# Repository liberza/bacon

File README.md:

# bacon - Balloon Ascent Controller

The goal of this project is to control the rate of ascent of two high-altitude
balloons, to keep at the same relative altitude as they ascend. 

A simulator is included in simulator/. Run tongs.py to start, then open client.html
in a browser. Power up the two payloads to begin auto-discovery. Once that is finished, 
the simulated flight begins and shows a live plot of progress.

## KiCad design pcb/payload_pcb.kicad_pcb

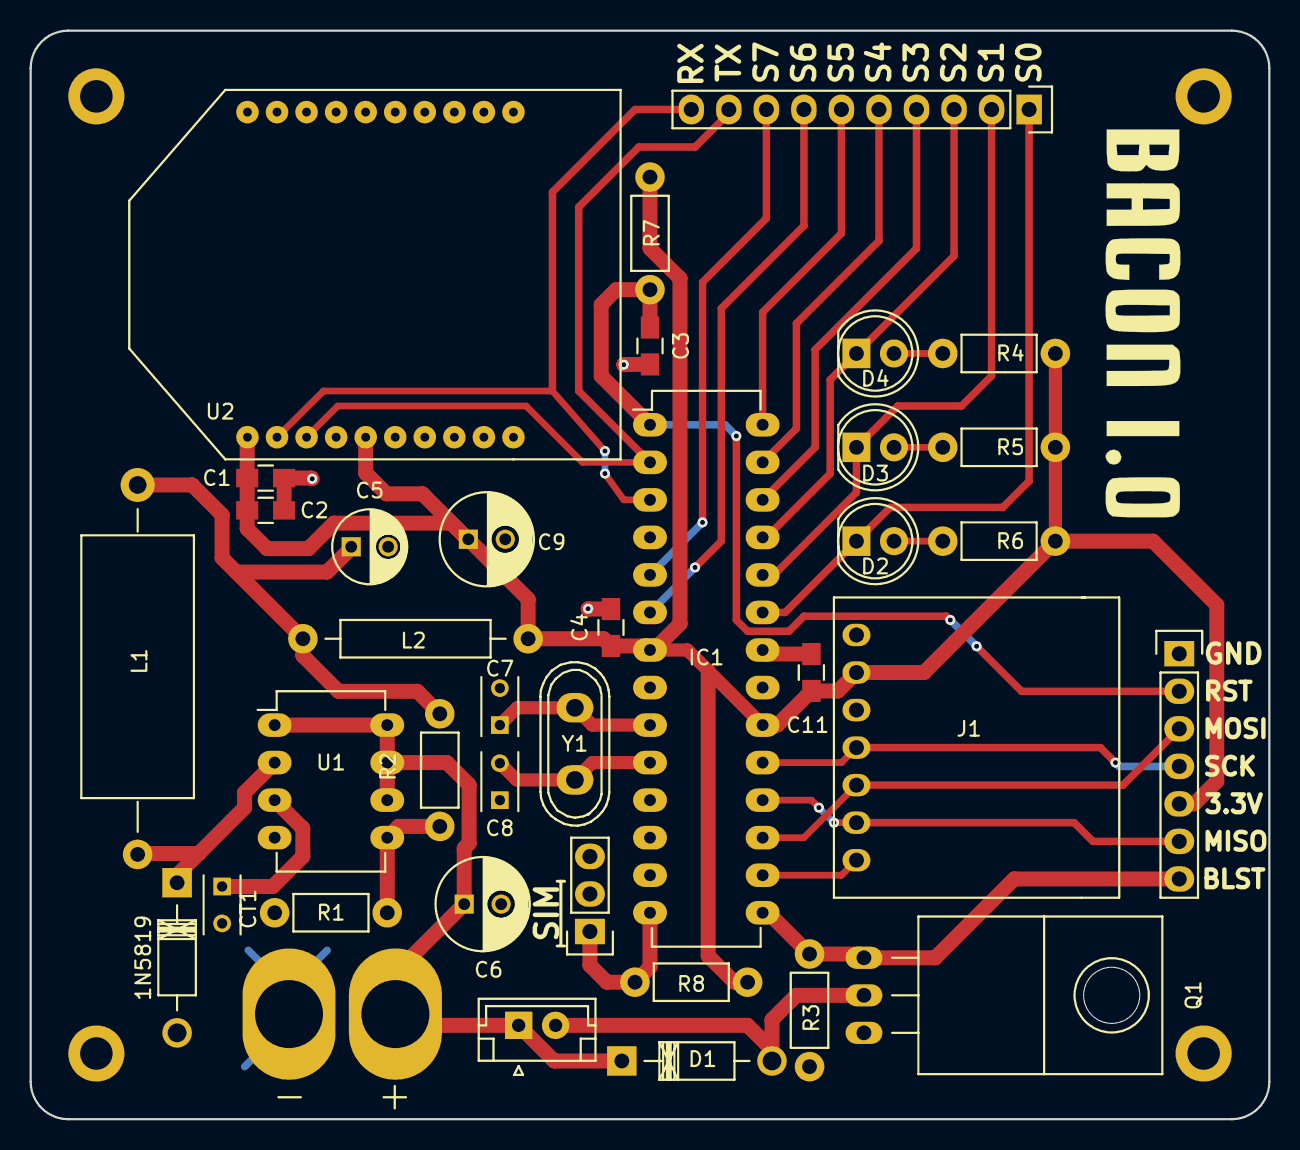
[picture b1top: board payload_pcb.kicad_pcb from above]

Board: 2 copper layers, 83.8 x 73.7 mm, 37 parts (0 on the bottom side), 30 nets.

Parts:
1N5819: D5; Diode_DO-41_SOD81_Horizontal_RM10
C1, C2, C4, C11: CP1; C_0805_HandSoldering
C3: 0.1uF; C_0805_HandSoldering
C5: 22uF; C_Radial_D5_L11_P2.5
C6: 100 uF; C_Radial_D6.3_L11.2_P2.5
C7, C8: 22p; C_Rect_L4_W2.5_P2.5
C9: 100uF; C_Radial_D6.3_L11.2_P2.5
CT1: 160 pF; C_Rect_L4_W2.5_P2.5
D1: D; Diode_DO-41_SOD81_Horizontal_RM10
D2: Green; LED-5MM
D3: Yellow; LED-5MM
D4: Red; LED-5MM
IC1: ATMEGA328-P; DIP-28_W7.62mm_LongPads
J1: MS5607_Module
L1: 50 uH; Choke_Horizontal_RM25mm
L2: 1 uH; Choke_Horizontal_RM15mm
P1: BAT_TERMINALS; XT60
P2: CONN_01X10; Pin_Header_Straight_1x10
P3: CONN_01X03; Pin_Header_Straight_1x03
P4: CONN_01X07; Pin_Header_Straight_1x07
P5: VALVE; JST_EH_B02B-EH-A_02x2.50mm_Straight
Q1: Q1; TO-220_Neutral123_Horizontal
R1: 22k; Resistor_Horizontal_RM7mm
R2: 36k; Resistor_Horizontal_RM7mm
R3, R7: 4.7k; Resistor_Horizontal_RM7mm
R4, R5, R6: 270; Resistor_Horizontal_RM7mm
R8: 4.7K; Resistor_Horizontal_RM7mm
U1: MC33063A; DIP-8_W7.62mm_LongPads
U2: XBee_S3B
Y1: Crystal; Crystal_HC50-U_Vertical

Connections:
3.3V: C1.1, C2.1, C4.1, C9.1, C11.1, IC1.7, IC1.20, J1.2, L2.1, P4.5, R4.2, R5.2, R6.2, R7.1, R8.1, U2.1, U2.5
BALLAST: IC1.15, P4.7, Q1.1, R3.1
CSB: IC1.16, J1.7
GND: 1N5819.2, C1.2, C2.2, C3.2, C4.2, C5.2, C6.2, C7.2, C8.1, C9.2, C11.2, CT1.2, IC1.8, IC1.22, J1.1, J1.3, P1.1, P3.2, P3.3, P4.1, Q1.3, R1.2, R3.2, U1.4, U2.10
MISO: IC1.18, J1.6, P4.6
MODE: IC1.14, P3.1, R8.2
MOSI: IC1.17, J1.5, P4.3
unnamed: 1N5819.1, L1.1, U1.2
unnamed: C5.1, L1.2, L2.2, R2.2
unnamed: C7.1, IC1.9, Y1.1
unnamed: C8.2, IC1.10, Y1.2
unnamed: CT1.1, U1.3
unnamed: D1.2, P5.2, Q1.2
unnamed: D2.2, R6.1
unnamed: D3.2, R5.1
unnamed: D4.2, R4.1
unnamed: R1.1, R2.1, U1.5
RESET: C3.1, IC1.1, P4.2, R7.2
SCK: IC1.19, J1.4, P4.4
STATUS0: D2.1, IC1.23, P2.1
STATUS1: D3.1, IC1.24, P2.2
STATUS2: D4.1, IC1.25, P2.3
STATUS3: IC1.26, P2.4
STATUS4: IC1.27, P2.5
STATUS5: IC1.28, P2.6
STATUS6: IC1.6, P2.7
STATUS7: IC1.5, P2.8
VDD: C6.1, D1.1, P1.2, P5.1, U1.1, U1.6, U1.7, U1.8
XBEE_RX: IC1.3, P2.10, U2.2
XBEE_TX: IC1.2, P2.9, U2.3

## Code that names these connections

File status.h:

#ifndef STATUS_H
#define STATUS_H

#include <stdint.h>

// Serial errors
#define DATA_BITS_ERR   (uint8_t)(0x01)
#define STOP_BITS_ERR   (uint8_t)(0x02)
#define PARITY_ERR      (uint8_t)(0x04)

// Memory errors
#define OOM_ERR         (uint8_t)(0x08)

// Frame errors
#define FRAME_SIZE_ERR  (uint8_t)(0x10)
#define FRAME_DELIM_ERR (uint8_t)(0x20)
#define FRAME_SUM_ERR   (uint8_t)(0x40)

#define STATUS0         (uint8_t)(0x01)
#define STATUS1         (uint8_t)(0x02)
#define STATUS2         (uint8_t)(0x04)
#define STATUS3         (uint8_t)(0x08)
#define STATUS4         (uint8_t)(0x10)
#define STATUS5         (uint8_t)(0x20)
#define STATUS6         (uint8_t)(0x40)
#define STATUS7         (uint8_t)(0x80)

//! Initialize GPIO for outputting error values.
void status_pin_init();

void drive_pins(uint8_t pins);

#endif

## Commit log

2016-09-11 Add profiles from UMHAB48 and UMHAB52, as well as code for parsing more profiles.
2016-09-11 added alts() method to AltitudeProfile class.
2016-09-11 save altitude values as floats instead of strings..
2016-09-11 rename ascent -> flight
2016-09-11 move profiles to their own dir
2016-09-11 add gitignore for tongs, using virtualenv now.
2016-09-11 add xbee.py and deps.txt
2016-09-16 rename to simulator
2016-09-21 add simple echo test for xbee comms. works.
2016-10-11 rename test, add serial.h
2016-10-11 rename test
2016-10-11 add endif
2016-10-11 add serial.c. modify definition of serial_init() to allow for easier configuration of UART.
2016-10-11 accidentally a semicolon
2016-10-11 add error handling
2016-10-11 formatting and comments
2016-10-11 cleanup
2016-10-11 always return a value from serial_init()
2016-10-15 working on escape function and init in xbee.py
2016-10-15 add escape() and unescape()
2016-10-15 comments on xbee.py
2016-10-16 much progress on XBee.tx(). untested beyond watching the TX LED light up on the breakout board when running it.
2016-10-16 functions for initializing gpio and operating solenoid valve
2016-10-16 add XBee.rx(). need to do frame validation
2016-10-16 fixed a few bugs. checksum now verifies correctly and length is computed properly
2016-10-16 reorganize constants, add new FRAME_TYPES dict of constants.
2016-10-16 interrupt reads byte and writes to buffer.
2016-10-16 simplified interrupt routine
2016-10-23 fix all compilation warnings and errors. ISR() is a macro, not a function to declare.
2016-10-23 add xbee.c
2016-10-23 add function declarations to xbee.h
2016-10-23 add pingpong.h
2016-10-23 add pingpong.c
2016-10-23 fix warnings and errors in pingpong
2016-10-23 set write index to 0 after swapping pingpong chunks
2016-10-23 integrating pingpong into serial
2016-10-23 rx_buf should be a pointer
2016-10-23 shiny new Makefile kifed from https://github.com/hexagon5un/AVR-Programming
2016-10-23 move ISR for rx to xbee.c, because it will swap buffers when frame delimiter is reached.
2016-10-23 use SPECIAL_BYTES instead of hardcoding frame delim
2016-10-23 add escape and unescape functions to xbee, progress on rx()
2016-10-23 move ready flag to pingpong
2016-10-24 add validate_frame()
2016-10-24 oops, add xbee.h
2016-10-24 add status.h and status.c
2016-10-24 remove status.o
2016-10-24 fix frame_types and special_bytes declarations
2016-10-27 add controller.h
2016-10-27 rename FlightProfile to Flight
2016-10-27 add flight.py back
2016-10-27 add sim.py
2016-10-27 make interrupt rx buffer volatile
2016-11-05 add tx() to xbee.c, and trying some tests.
2016-11-06 replacing pingpong.h/c with rbuf.h/c. a ring buffer is more appropriate for this use-case.
2016-11-06 further modifications incorporating rbuf. this will be much better.
2016-11-06 make rbuf operations atomic!
2016-11-06 rbuf tweaks
2016-11-06 rbuf now replaces pingpong. fixed all warnings and errors. untested.
2016-11-11 change status lines. debugging.
2016-11-11 fix xbee.py. seems to work great now.
2016-11-11 fix frame parsing
2016-11-11 fixing parse frame and checksum in xbee.py. also confirmed that unescaping in xbee.c seems to work fine.
2016-11-11 xbee.c tx() works. added check for TX in xbee.py for debugging.
2016-11-13 Found a potential root cause for validate_frame() not working correctly. Was not shifting the rbuf on fail conditions, so it would just fail again, and again, and again, and again, and again, and aga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
2016-11-13 disable interrupts during tx
2016-11-13 Fix a few rbuf oddities. Incorrect shifting...
2016-11-13 better approach to escaping.
2016-11-13 Found bug, in process of squashing. Was abusing ATOMIC_BLOCK(). Probably don't even need it.
2016-11-13 frame parsing mostly working. some strange repetition going on, but the meat is all there.
2016-11-14 Just spent 7 hours fixing the resend bug. It has been squashed.
2016-11-14 nicer xbee.py escaping
2016-11-14 fixed bug where validate_frame() thought the frame was larger than it actually was, when multiple bytes were escaped.
2016-11-15 add Bacon Message Protocol file.
2016-11-15 add flight profiles back.
2016-11-15 hadn't added the main file. awkward.
2016-11-15 add nice lil scripts for resetting buspirate.. These are for the build process, not related to the rest of the project at all.
2016-11-15 bmp.py is just about there. let's try it out.
2016-11-15 rename flight.py to payload.py. why not?
2016-11-15 sending WAT requests seems to work. now let's get the AVR side of things working.
2016-11-15 add bmp.h
2016-11-15 add bmp.c.
2016-11-15 fix warnings and errors in bmp.c.
2016-11-15 BMP works between sim and payload. Let's try Sbetween two payloads now.
2016-11-15 We have inter-payload communication.
2016-11-15 reoganize a bit. rename wat() to init_peering() and move to bmp.py
2016-11-16 altimeter code, without testing and without conversion
2016-11-16 Fixed error; code compiles
2016-11-16 add curve-fitted timestep adjustment function
2016-11-16 simulator is essentially there. now for the AVR side of things.
2016-11-16 simple timers are working.
2016-11-16 rewriting altitude code from scratch
2016-11-16 fixed redefinition
2016-11-16 initialized variables and fixed more errors
2016-11-17 added function for reading sensor adc
2016-11-17 added PROM read function and fixed errors
2016-11-17 removed possible crc function
2016-11-17 initialized PB1 to 0 before setting as output
2016-11-17 completed function for returning atmospheric pressure (untested)
2016-11-17 possible finished altitude calculations; ready to test
2016-11-17 Simulator appears to be accurate.
2016-11-17 Ready for control.
2016-11-17 add controller, oops
2016-11-17 remove controller.o
2016-11-17 added unique proportional controller
2016-11-17 main() improvements
2016-11-17 The controller does, in fact, control.
2016-11-17 tweak controller parameter to give more responsive control
2016-11-23 tweak control params.
2016-12-10 update makefile. turn on optimization, and add lines to support another programmer. also adding comments in xbee.c. also, more solenoid testing in main.c.
2016-12-10 add tests/ dir and test_solenoid.c along with new makefile for tests.
2016-12-10 add lib/ dir to contain all of bacon's modules.
2016-12-10 green LED now blinks while in peering mode, stays solid while in flight
2016-12-10 remove object files
2016-12-11 Better makefile organization for tests.
2016-12-11 basic test for altimeter
2016-12-11 added buspirate power
2016-12-11 fixed bug where peering would loop infinitely.
2016-12-12 fix buffer overflow in frame parsing.
2016-12-12 Add live graphs. Tweak control params. Reduce threshold to 5 meters.
2016-12-12 add liveplot.py
2016-12-12 Tweak control params. Set frame ID to 0x00 to avoid TX_STATUS packets, this has seriously improved transmission reliability.
2016-12-12 Tweak control params a bit more. Getting close. Need to reduce RX timeout time to improve simulated altitude consistency.
2016-12-12 Peering reliability improved. Also decreased all timeouts and timer thresholds, the XBees and AVRs can handle it and it makes everything more responsive.
2016-12-12 Cleanup Makefile, merge test makefile into main one
2016-12-12 remove scripts irrelevant to the project
2016-12-12 cleaning up. adding comments and removing old sections.
2016-12-12 adjusted functions for debugging
2016-12-12 more detailed test of altimeter
2016-12-12 cleaning up. looks good.
2016-12-12 cleaning up sim a bit.
2016-12-12 More cleanup. Looking good, time to print it
2016-12-12 successfully reading pressure (bar) and temperature (celsius)
2016-12-12 removed two functions for testing
2016-12-13 add pcb files
2017-03-31 temporarily turn off graph, change print style
2017-03-31 add sliding window average to prev_dist and prev_delta_dist calculations in controller.
2017-03-31 only save 3 previous dists for the average. taken every 5 seconds.
2017-03-31 Increase D in control, reduce threshold, and reduce number of samples for averaging. Also, harden the xbee code against edge case where frame length = MAX_BUF_LEN.
2017-04-02 Now serving data over websockets. Access chart through js/html. Also, control parameter tweak.
2017-04-02 add JS client and smoothie dependency.
2017-04-02 Calibrate control parameters more. Best yet. Changed payload ballast to 1L.
2017-04-02 peering improvements
2017-04-03 tweaks to chart client
2017-04-06 TONGS ui tweaks
2017-04-06 add listen.py
2017-04-06 oops, tongs wasn't added back after renaming.
2017-04-09 Troubleshooting the altimeter
2017-04-10 Controller parameters make ballast last past 30000m. schweet
2017-04-12 Fix locking in code. Also some tongs updates.
2017-04-27 successfully reading alt in dm
2017-04-27 flight/sim mode modifications
2017-04-27 removed test code
2017-04-27 fix conflict between get_alt() and parse_alt()
2017-04-27 implemented functions
2017-04-27 flight mode modifications
2017-04-27 more cleanup...
2017-04-29 was having an issue with flight mode... the issue was = instead of ==...
2017-04-29 Fixed a lot of things........ like flight mode, altimeter calibration, initializing memory...
